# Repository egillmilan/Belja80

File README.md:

# Belja80
 
TKL keyboard based on the RP2040 microcontroller. Compatible with ANSI and ISO layout.

# Flashing instructions
* Plug the keyboard into a computer and a drive named "RP2040" should appear. It might be necessary to hold down the boot button while plugging in the board for the drive to appear.
* Install [Adafruit circuitpython for the Raspberry Pi Pico](https://circuitpython.org/board/raspberry_pi_pico/), version 8 or newer. This is done by copying the .uf2 file to the RP2040 drive. The drive will dissapear briefly and a drive named "CIRCUITPY" will appear.
* Copy the folder named "kmk" from the [kmk_firmware-master repository](https://github.com/KMKfw/kmk_firmware) to the CIRCUIUTPY drive.
* Copy the supplied python files in the "Belja80_firmware" folder to the CIRCUITPY drive.

The keyboard should now work. When plugging in the keyboard next time, the board will not appear as a drive. To let the keyboard appear as a drive, hold in Esc while plugging the keyboard into your computer.

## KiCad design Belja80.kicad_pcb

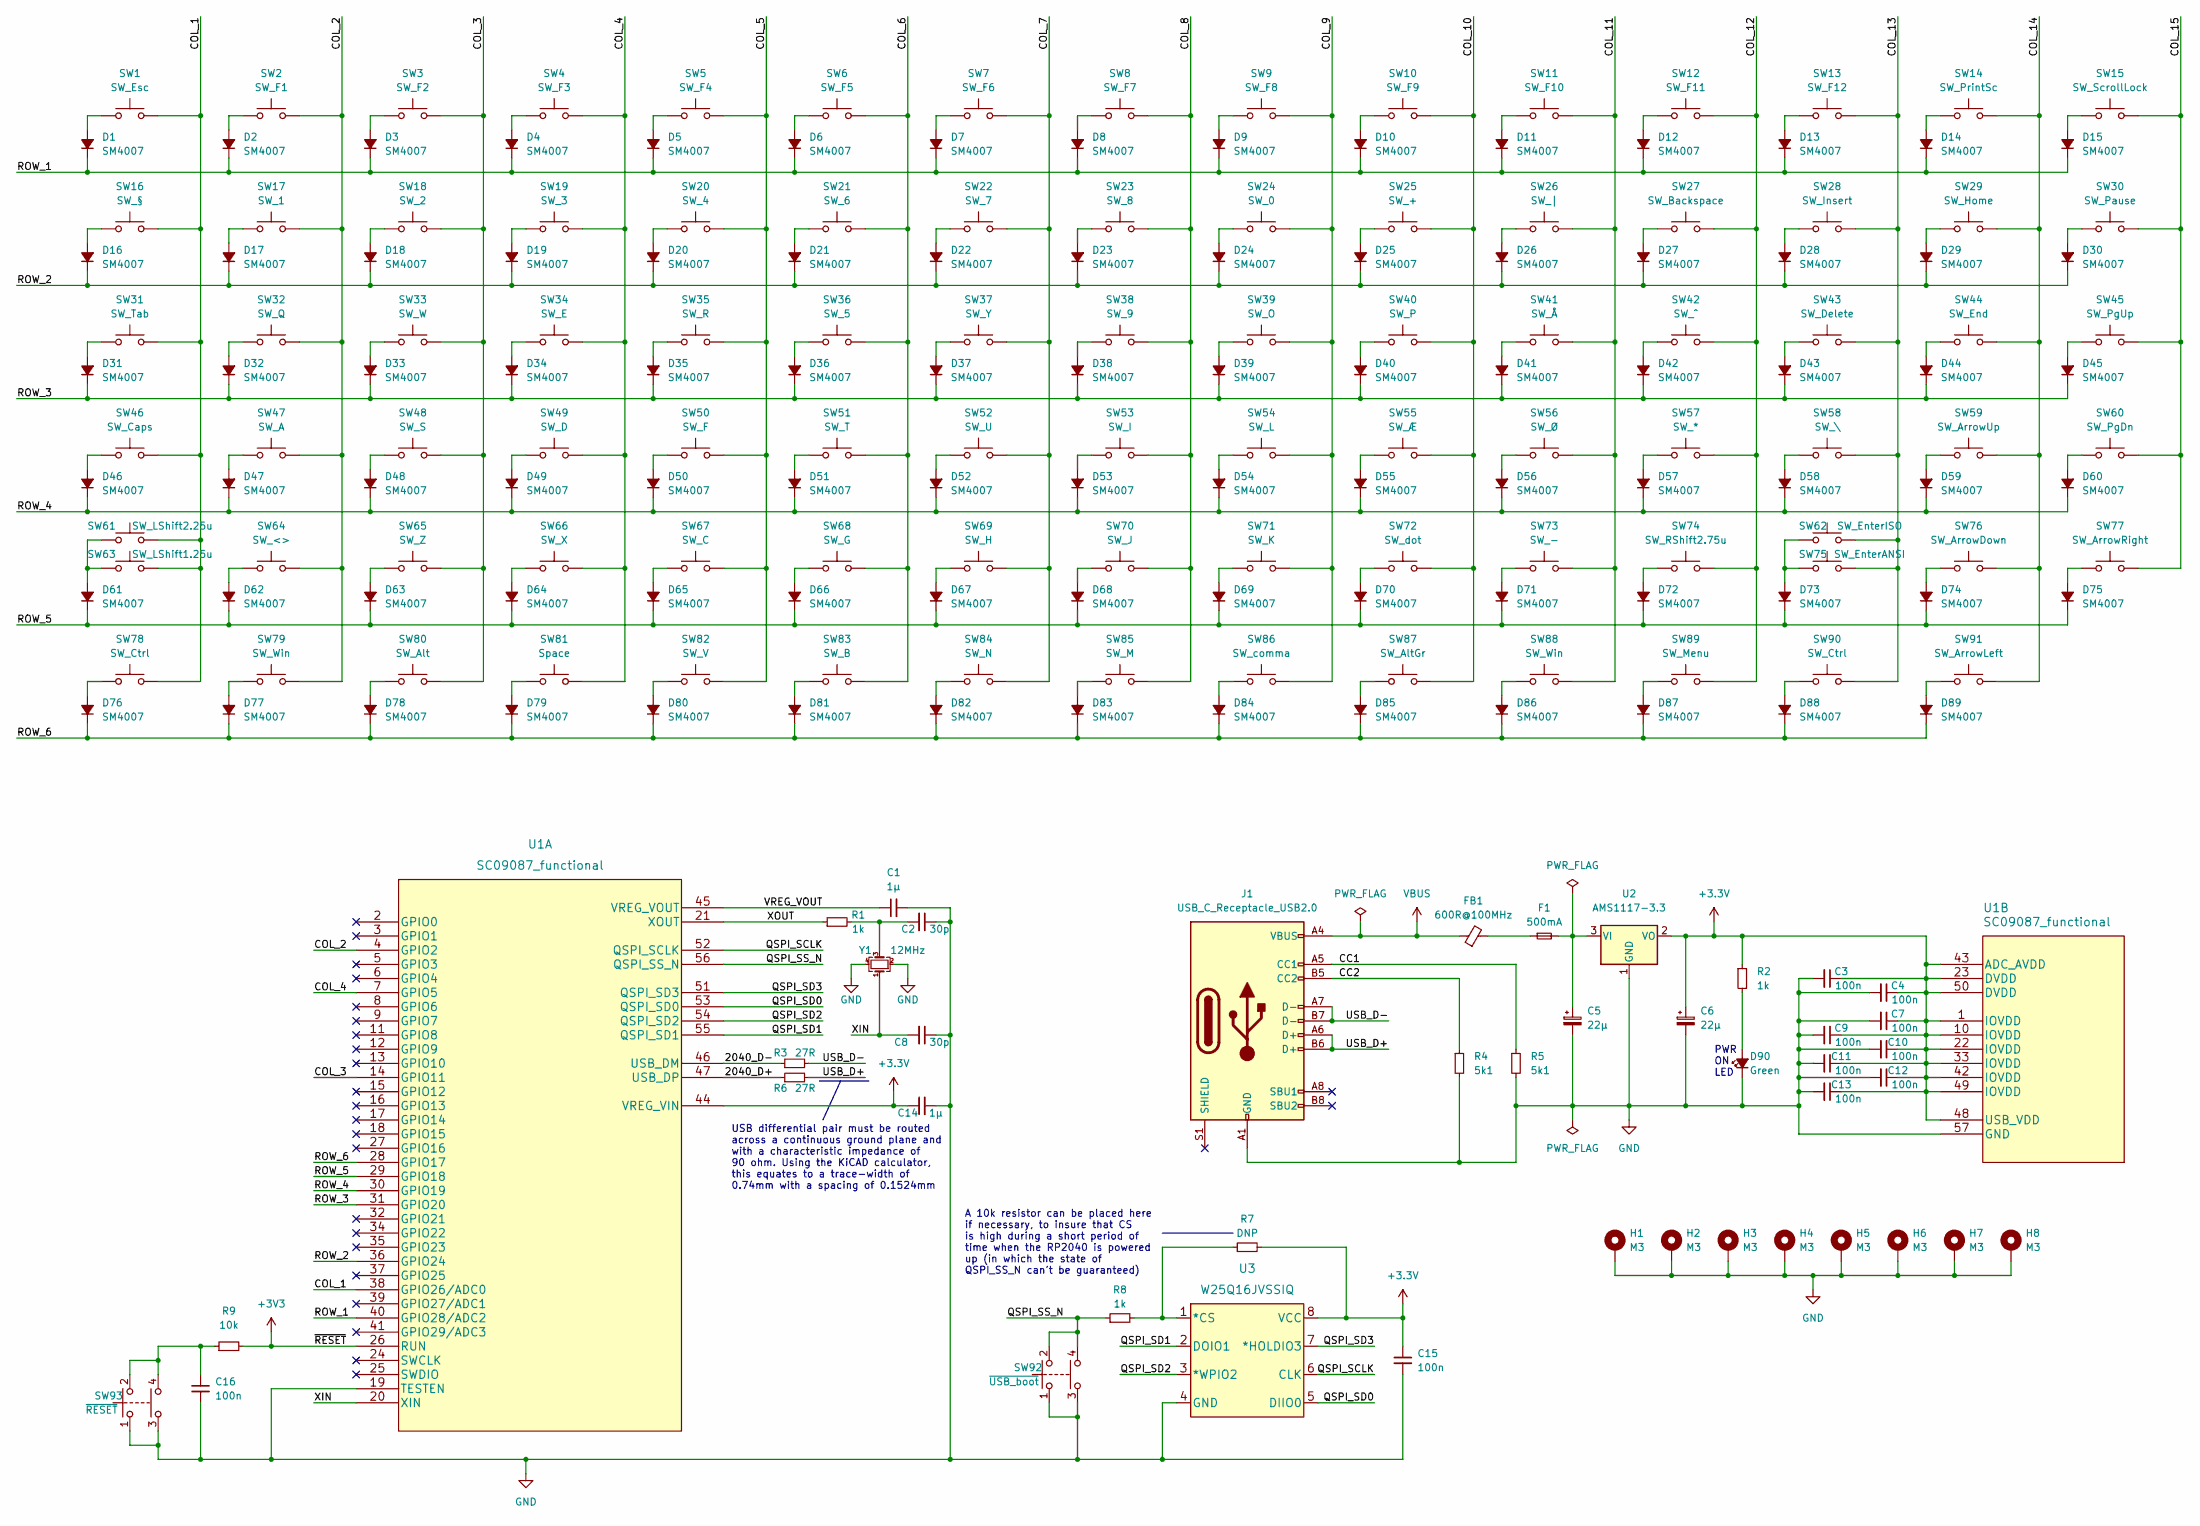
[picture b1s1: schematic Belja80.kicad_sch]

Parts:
C1, C14: 1µ; C_0402_1005Metric
C2, C8: 30p; C_0402_1005Metric
C3, C4, C7, C9, C10, C11, C12, C13, C15, C16: 100n; C_0402_1005Metric
C5, C6: 22µ; CP_EIA-3216-18_Kemet-A
D1, D2, D3, D4, D5, D6, D7, D8, D9, D10, D11, D12, D13, D14, D15, D16, D17, D18, D19, D20, D21, D22, D23, D24, D25, D26, D27, D28, D29, D30, D31, D32, D33, D34, D35, D36, D37, D38, D39, D40, D41, D42, D43, D44, D45, D46, D47, D48, D49, D50, D51, D52, D53, D54, D55, D56, D57, D58, D59, D60, D61, D62, D63, D64, D65, D66, D67, D68, D69, D70, D71, D72, D73, D74, D75, D76, D77, D78, D79, D80, D81, D82, D83, D84, D85, D86, D87, D88, D89: SM4007; D_SOD-123F
D90: Green; LED_0603_1608Metric
F1: 500mA; Fuse_1206_3216Metric
FB1: 600R@100MHz; L_0603_1608Metric
H1, H2, H3, H4, H5, H6, H7, H8: M3; MountingHole_3.2mm_M3_Pad_Via
J1: USB_C_Receptacle_USB2.0; USB_C_Receptacle_GCT_USB4085
R1, R2, R8: 1k; R_0603_1608Metric
R3, R6: 27R; R_0603_1608Metric
R4, R5: 5k1; R_0603_1608Metric
R7: DNP; R_0603_1608Metric
R9: 10k; R_0603_1608Metric
SW1: SW_Esc; SW_Cherry_MX_1.00u_PCB
SW2: SW_F1; SW_Cherry_MX_1.00u_PCB
SW3: SW_F2; SW_Cherry_MX_1.00u_PCB
SW4: SW_F3; SW_Cherry_MX_1.00u_PCB
SW5: SW_F4; SW_Cherry_MX_1.00u_PCB
SW6: SW_F5; SW_Cherry_MX_1.00u_PCB
SW7: SW_F6; SW_Cherry_MX_1.00u_PCB
SW8: SW_F7; SW_Cherry_MX_1.00u_PCB
SW9: SW_F8; SW_Cherry_MX_1.00u_PCB
SW10: SW_F9; SW_Cherry_MX_1.00u_PCB
SW11: SW_F10; SW_Cherry_MX_1.00u_PCB
SW12: SW_F11; SW_Cherry_MX_1.00u_PCB
SW13: SW_F12; SW_Cherry_MX_1.00u_PCB
SW14: SW_PrintSc; SW_Cherry_MX_1.00u_PCB
SW15: SW_ScrollLock; SW_Cherry_MX_1.00u_PCB
SW16: SW_§; SW_Cherry_MX_1.00u_PCB
SW17: SW_1; SW_Cherry_MX_1.00u_PCB
SW18: SW_2; SW_Cherry_MX_1.00u_PCB
SW19: SW_3; SW_Cherry_MX_1.00u_PCB
SW20: SW_4; SW_Cherry_MX_1.00u_PCB
SW21: SW_6; SW_Cherry_MX_1.00u_PCB
SW22: SW_7; SW_Cherry_MX_1.00u_PCB
SW23: SW_8; SW_Cherry_MX_1.00u_PCB
SW24: SW_0; SW_Cherry_MX_1.00u_PCB
SW25: SW_+; SW_Cherry_MX_1.00u_PCB
SW26: SW_|; SW_Cherry_MX_1.00u_PCB
SW27: SW_Backspace; SW_Cherry_MX_2.00u_PCB
SW28: SW_Insert; SW_Cherry_MX_1.00u_PCB
SW29: SW_Home; SW_Cherry_MX_1.00u_PCB
SW30: SW_Pause; SW_Cherry_MX_1.00u_PCB
SW31: SW_Tab; SW_Cherry_MX_1.50u_PCB
SW32: SW_Q; SW_Cherry_MX_1.00u_PCB
SW33: SW_W; SW_Cherry_MX_1.00u_PCB
SW34: SW_E; SW_Cherry_MX_1.00u_PCB
SW35: SW_R; SW_Cherry_MX_1.00u_PCB
SW36: SW_5; SW_Cherry_MX_1.00u_PCB
SW37: SW_Y; SW_Cherry_MX_1.00u_PCB
SW38: SW_9; SW_Cherry_MX_1.00u_PCB
SW39: SW_O; SW_Cherry_MX_1.00u_PCB
SW40: SW_P; SW_Cherry_MX_1.00u_PCB
SW41: SW_Å; SW_Cherry_MX_1.00u_PCB
SW42: SW_^; SW_Cherry_MX_1.00u_PCB
SW43: SW_Delete; SW_Cherry_MX_1.00u_PCB
SW44: SW_End; SW_Cherry_MX_1.00u_PCB
SW45: SW_PgUp; SW_Cherry_MX_1.00u_PCB
SW46: SW_Caps; SW_Cherry_MX_1.75u_PCB
SW47: SW_A; SW_Cherry_MX_1.00u_PCB
SW48: SW_S; SW_Cherry_MX_1.00u_PCB
SW49: SW_D; SW_Cherry_MX_1.00u_PCB
SW50: SW_F; SW_Cherry_MX_1.00u_PCB
SW51: SW_T; SW_Cherry_MX_1.00u_PCB
SW52: SW_U; SW_Cherry_MX_1.00u_PCB
SW53: SW_I; SW_Cherry_MX_1.00u_PCB
SW54: SW_L; SW_Cherry_MX_1.00u_PCB
SW55: SW_Æ; SW_Cherry_MX_1.00u_PCB
SW56: SW_Ø; SW_Cherry_MX_1.00u_PCB
SW57: SW_*; SW_Cherry_MX_1.00u_PCB
SW58: SW_\; SW_Cherry_MX_1.50u_PCB
SW59: SW_ArrowUp; SW_Cherry_MX_1.00u_PCB
SW60: SW_PgDn; SW_Cherry_MX_1.00u_PCB
SW61: SW_LShift2.25u; SW_Cherry_MX_2.25u_PCB
SW62: SW_EnterISO; SW_Cherry_MX_ISOEnter_PCB
SW63: SW_LShift1.25u; SW_Cherry_MX_1.25u_PCB
SW64: SW_<>; SW_Cherry_MX_1.00u_PCB
SW65: SW_Z; SW_Cherry_MX_1.00u_PCB
SW66: SW_X; SW_Cherry_MX_1.00u_PCB
SW67: SW_C; SW_Cherry_MX_1.00u_PCB
SW68: SW_G; SW_Cherry_MX_1.00u_PCB
SW69: SW_H; SW_Cherry_MX_1.00u_PCB
SW70: SW_J; SW_Cherry_MX_1.00u_PCB
SW71: SW_K; SW_Cherry_MX_1.00u_PCB
SW72: SW_dot; SW_Cherry_MX_1.00u_PCB
SW73: SW_-; SW_Cherry_MX_1.00u_PCB
SW74: SW_RShift2.75u; SW_Cherry_MX_2.75u_PCB
SW75: SW_EnterANSI; SW_Cherry_MX_2.25u_PCB
SW76: SW_ArrowDown; SW_Cherry_MX_1.00u_PCB
SW77: SW_ArrowRight; SW_Cherry_MX_1.00u_PCB
SW78, SW90: SW_Ctrl; SW_Cherry_MX_1.25u_PCB
SW79, SW88: SW_Win; SW_Cherry_MX_1.25u_PCB
SW80: SW_Alt; SW_Cherry_MX_1.25u_PCB
SW81: Space; SW_Cherry_MX_6.25u_PCB
SW82: SW_V; SW_Cherry_MX_1.00u_PCB
SW83: SW_B; SW_Cherry_MX_1.00u_PCB
SW84: SW_N; SW_Cherry_MX_1.00u_PCB
SW85: SW_M; SW_Cherry_MX_1.00u_PCB
SW86: SW_comma; SW_Cherry_MX_1.00u_PCB
SW87: SW_AltGr; SW_Cherry_MX_1.25u_PCB
SW89: SW_Menu; SW_Cherry_MX_1.25u_PCB
SW91: SW_ArrowLeft; SW_Cherry_MX_1.00u_PCB
SW92: ~{USB_boot}; SW_TS-1187A-B-A-B
SW93: ~{RESET}; SW_TS-1187A-B-A-B
U1: SC09087_functional; SC09087
U2: AMS1117-3.3; SOT-223-3_TabPin2
U3: W25Q16JVSSIQ
Y1: 12MHz; Crystal_SMD_3225-4Pin_3.2x2.5mm

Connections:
/2040_D+: R6.1, U1.47 (USB_DP)
/2040_D-: R3.1, U1.46 (USB_DM)
/CC1: J1.A5 (CC1), R5.1
/CC2: J1.B5 (CC2), R4.1
/COL_1: SW1.2, SW16.2, SW31.2, SW46.2, SW61.2, SW63.2, SW78.2, U1.38 (GPIO26/ADC0)
/COL_2: SW2.2, SW17.2, SW32.2, SW47.2, SW64.2, SW79.2, U1.4 (GPIO2)
/COL_3: SW3.2, SW18.2, SW33.2, SW48.2, SW65.2, SW80.2, U1.14 (GPIO11)
/COL_4: SW4.2, SW19.2, SW34.2, SW49.2, SW66.2, SW81.2, U1.7 (GPIO5)
/COL_5: SW5.2, SW20.2, SW35.2, SW50.2, SW67.2, SW82.2
/COL_6: SW6.2, SW21.2, SW36.2, SW51.2, SW68.2, SW83.2
/COL_7: SW7.2, SW22.2, SW37.2, SW52.2, SW69.2, SW84.2
/COL_8: SW8.2, SW23.2, SW38.2, SW53.2, SW70.2, SW85.2
/COL_9: SW9.2, SW24.2, SW39.2, SW54.2, SW71.2, SW86.2
/COL_10: SW10.2, SW25.2, SW40.2, SW55.2, SW72.2, SW87.2
/COL_11: SW11.2, SW26.2, SW41.2, SW56.2, SW73.2, SW88.2
/COL_12: SW12.2, SW27.2, SW42.2, SW57.2, SW74.2, SW89.2
/COL_13: SW13.2, SW28.2, SW43.2, SW58.2, SW62.2, SW75.2, SW90.2
/COL_14: SW14.2, SW29.2, SW44.2, SW59.2, SW76.2, SW91.2
/COL_15: SW15.2, SW30.2, SW45.2, SW60.2, SW77.2
/QSPI_SCLK: U1.52 (QSPI_SCLK), U3.6 (CLK)
/QSPI_SD0: U1.53 (QSPI_SD0), U3.5 (DIIO0)
/QSPI_SD1: U1.55 (QSPI_SD1), U3.2 (DOIO1)
/QSPI_SD2: U1.54 (QSPI_SD2), U3.3 (*WPIO2)
/QSPI_SD3: U1.51 (QSPI_SD3), U3.7 (*HOLDIO3)
/QSPI_SS_N: R8.1, SW92.2, SW92.4, U1.56 (QSPI_SS_N)
/ROW_1: D1.1 (K), D2.1 (K), D3.1 (K), D4.1 (K), D5.1 (K), D6.1 (K), D7.1 (K), D8.1 (K), D9.1 (K), D10.1 (K), D11.1 (K), D12.1 (K), D13.1 (K), D14.1 (K), D15.1 (K), U1.40 (GPIO28/ADC2)
/ROW_2: D16.1 (K), D17.1 (K), D18.1 (K), D19.1 (K), D20.1 (K), D21.1 (K), D22.1 (K), D23.1 (K), D24.1 (K), D25.1 (K), D26.1 (K), D27.1 (K), D28.1 (K), D29.1 (K), D30.1 (K), U1.36 (GPIO24)
/ROW_3: D31.1 (K), D32.1 (K), D33.1 (K), D34.1 (K), D35.1 (K), D36.1 (K), D37.1 (K), D38.1 (K), D39.1 (K), D40.1 (K), D41.1 (K), D42.1 (K), D43.1 (K), D44.1 (K), D45.1 (K), U1.31 (GPIO20)
/ROW_4: D46.1 (K), D47.1 (K), D48.1 (K), D49.1 (K), D50.1 (K), D51.1 (K), D52.1 (K), D53.1 (K), D54.1 (K), D55.1 (K), D56.1 (K), D57.1 (K), D58.1 (K), D59.1 (K), D60.1 (K), U1.30 (GPIO19)
/ROW_5: D61.1 (K), D62.1 (K), D63.1 (K), D64.1 (K), D65.1 (K), D66.1 (K), D67.1 (K), D68.1 (K), D69.1 (K), D70.1 (K), D71.1 (K), D72.1 (K), D73.1 (K), D74.1 (K), D75.1 (K), U1.29 (GPIO18)
/ROW_6: D76.1 (K), D77.1 (K), D78.1 (K), D79.1 (K), D80.1 (K), D81.1 (K), D82.1 (K), D83.1 (K), D84.1 (K), D85.1 (K), D86.1 (K), D87.1 (K), D88.1 (K), D89.1 (K), U1.28 (GPIO17)
/USB_D+: J1.A6 (D+), J1.B6 (D+), R6.2
/USB_D-: J1.A7 (D-), J1.B7 (D-), R3.2
/XIN: C8.2, U1.20 (XIN), Y1.1
/XOUT: R1.1, U1.21 (XOUT)
GND: C1.2, C2.1, C3.2, C4.2, C5.2, C6.2, C7.2, C8.1, C9.2, C10.2, C11.2, C12.2, C13.2, C14.2, C15.2, C16.2, D90.1 (K), H1.1, H2.1, H3.1, H4.1, H5.1, H6.1, H7.1, H8.1, J1.A1 (GND), J1.A12 (GND), J1.B1 (GND), J1.B12 (GND), R4.2, R5.2, SW92.1, SW92.3, SW93.1, SW93.3, U1.19 (TESTEN), U1.57 (GND), U2.1 (GND), U3.4 (GND), Y1.2, Y1.4
unnamed: C2.2, R1.2, Y1.3
unnamed: C16.1, R9.1, SW93.2, SW93.4
unnamed: D1.2 (A), SW1.1
unnamed: D2.2 (A), SW2.1
unnamed: D3.2 (A), SW3.1
unnamed: D4.2 (A), SW4.1
unnamed: D5.2 (A), SW5.1
unnamed: D6.2 (A), SW6.1
unnamed: D7.2 (A), SW7.1
unnamed: D8.2 (A), SW8.1
unnamed: D9.2 (A), SW9.1
unnamed: D10.2 (A), SW10.1
unnamed: D11.2 (A), SW11.1
unnamed: D12.2 (A), SW12.1
unnamed: D13.2 (A), SW13.1
unnamed: D14.2 (A), SW14.1
unnamed: D15.2 (A), SW15.1
unnamed: D16.2 (A), SW16.1
unnamed: D17.2 (A), SW17.1
unnamed: D18.2 (A), SW18.1
unnamed: D19.2 (A), SW19.1
unnamed: D20.2 (A), SW20.1
unnamed: D21.2 (A), SW21.1
unnamed: D22.2 (A), SW22.1
unnamed: D23.2 (A), SW23.1
unnamed: D24.2 (A), SW24.1
unnamed: D25.2 (A), SW25.1
unnamed: D26.2 (A), SW26.1
unnamed: D27.2 (A), SW27.1
unnamed: D28.2 (A), SW28.1
unnamed: D29.2 (A), SW29.1
unnamed: D30.2 (A), SW30.1
unnamed: D31.2 (A), SW31.1
unnamed: D32.2 (A), SW32.1
unnamed: D33.2 (A), SW33.1
unnamed: D34.2 (A), SW34.1
unnamed: D35.2 (A), SW35.1
unnamed: D36.2 (A), SW36.1
unnamed: D37.2 (A), SW37.1
unnamed: D38.2 (A), SW38.1
unnamed: D39.2 (A), SW39.1
unnamed: D40.2 (A), SW40.1
unnamed: D41.2 (A), SW41.1
unnamed: D42.2 (A), SW42.1
unnamed: D43.2 (A), SW43.1
unnamed: D44.2 (A), SW44.1
unnamed: D45.2 (A), SW45.1
unnamed: D46.2 (A), SW46.1
unnamed: D47.2 (A), SW47.1
unnamed: D48.2 (A), SW48.1
unnamed: D49.2 (A), SW49.1
unnamed: D50.2 (A), SW50.1
unnamed: D51.2 (A), SW51.1
unnamed: D52.2 (A), SW52.1
unnamed: D53.2 (A), SW53.1
unnamed: D54.2 (A), SW54.1
unnamed: D55.2 (A), SW55.1
unnamed: D56.2 (A), SW56.1
unnamed: D57.2 (A), SW57.1
unnamed: D58.2 (A), SW58.1
unnamed: D59.2 (A), SW59.1
unnamed: D60.2 (A), SW60.1
unnamed: D61.2 (A), SW61.1, SW63.1
unnamed: D62.2 (A), SW64.1
unnamed: D63.2 (A), SW65.1
unnamed: D64.2 (A), SW66.1
unnamed: D65.2 (A), SW67.1
unnamed: D66.2 (A), SW68.1
unnamed: D67.2 (A), SW69.1
unnamed: D68.2 (A), SW70.1
unnamed: D69.2 (A), SW71.1
unnamed: D70.2 (A), SW72.1
unnamed: D71.2 (A), SW73.1
unnamed: D72.2 (A), SW74.1
unnamed: D73.2 (A), SW62.1, SW75.1
unnamed: D74.2 (A), SW76.1
unnamed: D75.2 (A), SW77.1
unnamed: D76.2 (A), SW78.1
unnamed: D77.2 (A), SW79.1
unnamed: D78.2 (A), SW80.1
unnamed: D79.2 (A), SW81.1
unnamed: D80.2 (A), SW82.1
unnamed: D81.2 (A), SW83.1
unnamed: D82.2 (A), SW84.1
unnamed: D83.2 (A), SW85.1
unnamed: D84.2 (A), SW86.1
unnamed: D85.2 (A), SW87.1
unnamed: D86.2 (A), SW88.1
unnamed: D87.2 (A), SW89.1
unnamed: D88.2 (A), SW90.1
unnamed: D89.2 (A), SW91.1
unnamed: D90.2 (A), R2.2
unnamed: F1.1, FB1.2
unnamed: C5.1, F1.2, U2.3 (VI)
unnamed: R7.1, R8.2, U3.1 (*CS)
VBUS: FB1.1, J1.A4 (VBUS), J1.A9 (VBUS), J1.B4 (VBUS), J1.B9 (VBUS)

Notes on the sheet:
PWR ON LED
A 10k resistor can be placed here if necessary, to insure that CS is high during a short period of time when the RP2040 is powered up (in which the state of QSPI_SS_N can't be guaranteed)
USB differential pair must be routed across a continuous ground plane and with a characteristic impedance of 90 ohm. Using the KiCAD calculator, this equates to a trace-width of 0.74mm with a spacing of 0.1524mm

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
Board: 2 copper layers, 223 parts (124 on the bottom side), 134 nets, no tracks yet.

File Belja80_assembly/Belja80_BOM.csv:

Comment,Designator,Footprint,LCSC Part Number
1uF,"C1, C14",402,C52923
30p,"C2, C8",402,C1570
100nF,"C3, C4, C7, C9, C10, C11, C12, C13, C15, C16",402,C1525
22uF,"C5, C6",CASE-A-3216,C97062
SM4007PL,"D1, D2, D3, D4, D5, D6, D7, D8, D9, D10, D11, D12, D13, D14, D15, D16, D17, D18, D19, D20, D21, D22, D23, D24, D25, D26, D27, D28, D29, D30, D31, D32, D33, D34, D35, D36, D37, D38, D39, D40, D41, D42, D43, D44, D45, D46, D47, D48, D49, D50, D51, D52, D53, D54, D55, D56, D57, D58, D59, D60, D61, D62, D63, D64, D65, D66, D67, D68, D69, D70, D71, D72, D73, D74, D75, D76, D77, D78, D79, D80, D81, D82, D83, D84, D85, D86, D87, D88, D89",SOD-123FL,C64898
Green LED,D90,603,C72043
500mA,F1,1206,C206992
220R@100MHz,FB1,603,C80165
USB_C_Receptacle,J1,SMD,C2760486
1k,"R1, R2, R8",402,C11702
27R,"R3, R6",402,C226392
5k1,"R4, R5",603,C23186
10k,R9,603,C25804
TS-1187A-B-A-B,"SW92,SW93",SMD,C318884
RP2040,U1,LQFN-56(7x7),C2040
AMS1117-3.3,U2,SOT-223-3,C6186
W25Q16JVSSIQ,U3,SOIC-8-208mil,C82317
12MHz,Y1,SMD3225-4P,C9002

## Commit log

2023-02-14 Rough layout
2023-02-18 Component layout
2023-02-20 routing µC section and silkscreen
2023-02-21 Routing
2023-02-21 Final routing and decorations
2023-02-24 Stepped Caps Lock support
2023-02-27 Added plate
2023-02-27 Ready for production
2023-04-18 3D model
2023-07-08 Added case 3D files
